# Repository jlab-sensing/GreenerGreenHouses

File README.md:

# JLab - Greener Greenhouses Sensing Project

This repository contains concurrent work for the Greener Greenhouses research project.

## Repository Contents

- **MSP430**
  
    Contains a general library for the [TI MSP430FR5969](https://www.ti.com/tool/MSP-EXP430FR5969?DCMP=mcugen&HQS=ep-mcu-msp-mcugen-mspblog-pf1-en) microcontroller to communicate with the [HDC2021](https://www.ti.com/product/HDC2021?utm_source=google&utm_medium=cpc&utm_campaign=asc-null-null-GPN_EN-cpc-pf-google-wwe&utm_content=HDC2021&ds_k=HDC2021&DCM=yes&gclid=Cj0KCQjwrfymBhCTARIsADXTabmBxpIyiHJQwz-0fqVoGLloWWmzIEXDT699dNn-ivyHtGXB0x-GpR8aAtybEALw_wcB&gclsrc=aw.ds) Temperature and Humidity Sensor.
  
- **PassiveLiFiTag**

    Includes schematic files for a prototype of the Passive LiFi IoT tag using the TI MSP430FR5969 microcontroller

- **RH_T_Replacement_Board**

    Contains .ino test harness and data storage files for HDC2021 sensor testing using Arduino. Also contains Eagle hardware files for the GGH RH/T replacement board
    
- **LoRa_BoosterPack_Registers**

    Contains register names and settings for ETSI CAT1 869MHz. 1.2Kbps, 2-GFSK, 25Khz channel spacing, ETSI EN 300 220 CAT1 setting with the [CC1125 LoRa module Boosterpack](https://www.ti.com/tool/BOOSTXL-CC1125). Register names and values exported from [SmartRFStudio v7.0](https://www.ti.com/tool/SMARTRFTM-STUDIO) for packet Tx/Rx.

- **BeagleBoneBlack**

    Contains source code for Beaglebone Black development, specifically work on SPI to LoRa boosterpack compatability, and ModbusLib test code for server/client side testing.

  ## To Do

  - [x] Create specific README file for each directory
  - [ ] file cleanup - remove defunct or unnecessary files
  - [ ] Update root README when new directories are created
  - [x] Standardize naming conventions for each directory
  - [x] License Project under MIT

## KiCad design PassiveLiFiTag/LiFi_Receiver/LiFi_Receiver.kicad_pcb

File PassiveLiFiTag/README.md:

# PassiveLiFiTag

This directory contains hardware design files for the PassiveLiFiTag. These files are compatible with EAGLE 9.6.2.

## Files
- Library Source\ -- Contains the source files that were used to create the EAGLE library
- PassiveLiFiTag.brd -- PCB layout (not yet added)
- PassiveLiFiTag.lbr -- EAGLE library
- PassiveLiFiTag.sch -- Electrical schematic

## Instructions
**NOTE**: Currently the schematic is not yet finalized. It is populated with major components, but is not connected.

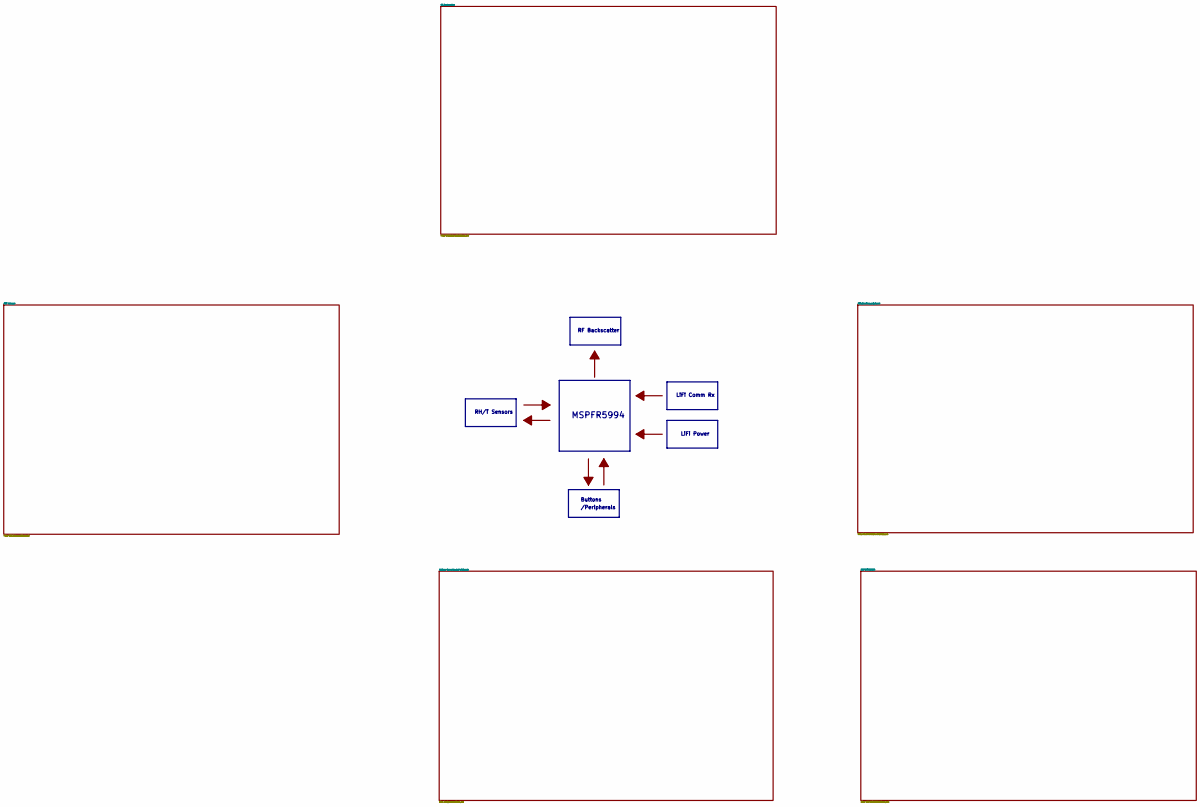
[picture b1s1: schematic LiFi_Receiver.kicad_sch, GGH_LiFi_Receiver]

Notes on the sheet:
RH/T Sensors
/Peripherals
LiFi Comm Rx
MSPFR5994
RF Backscatter
Buttons
LiFi Power

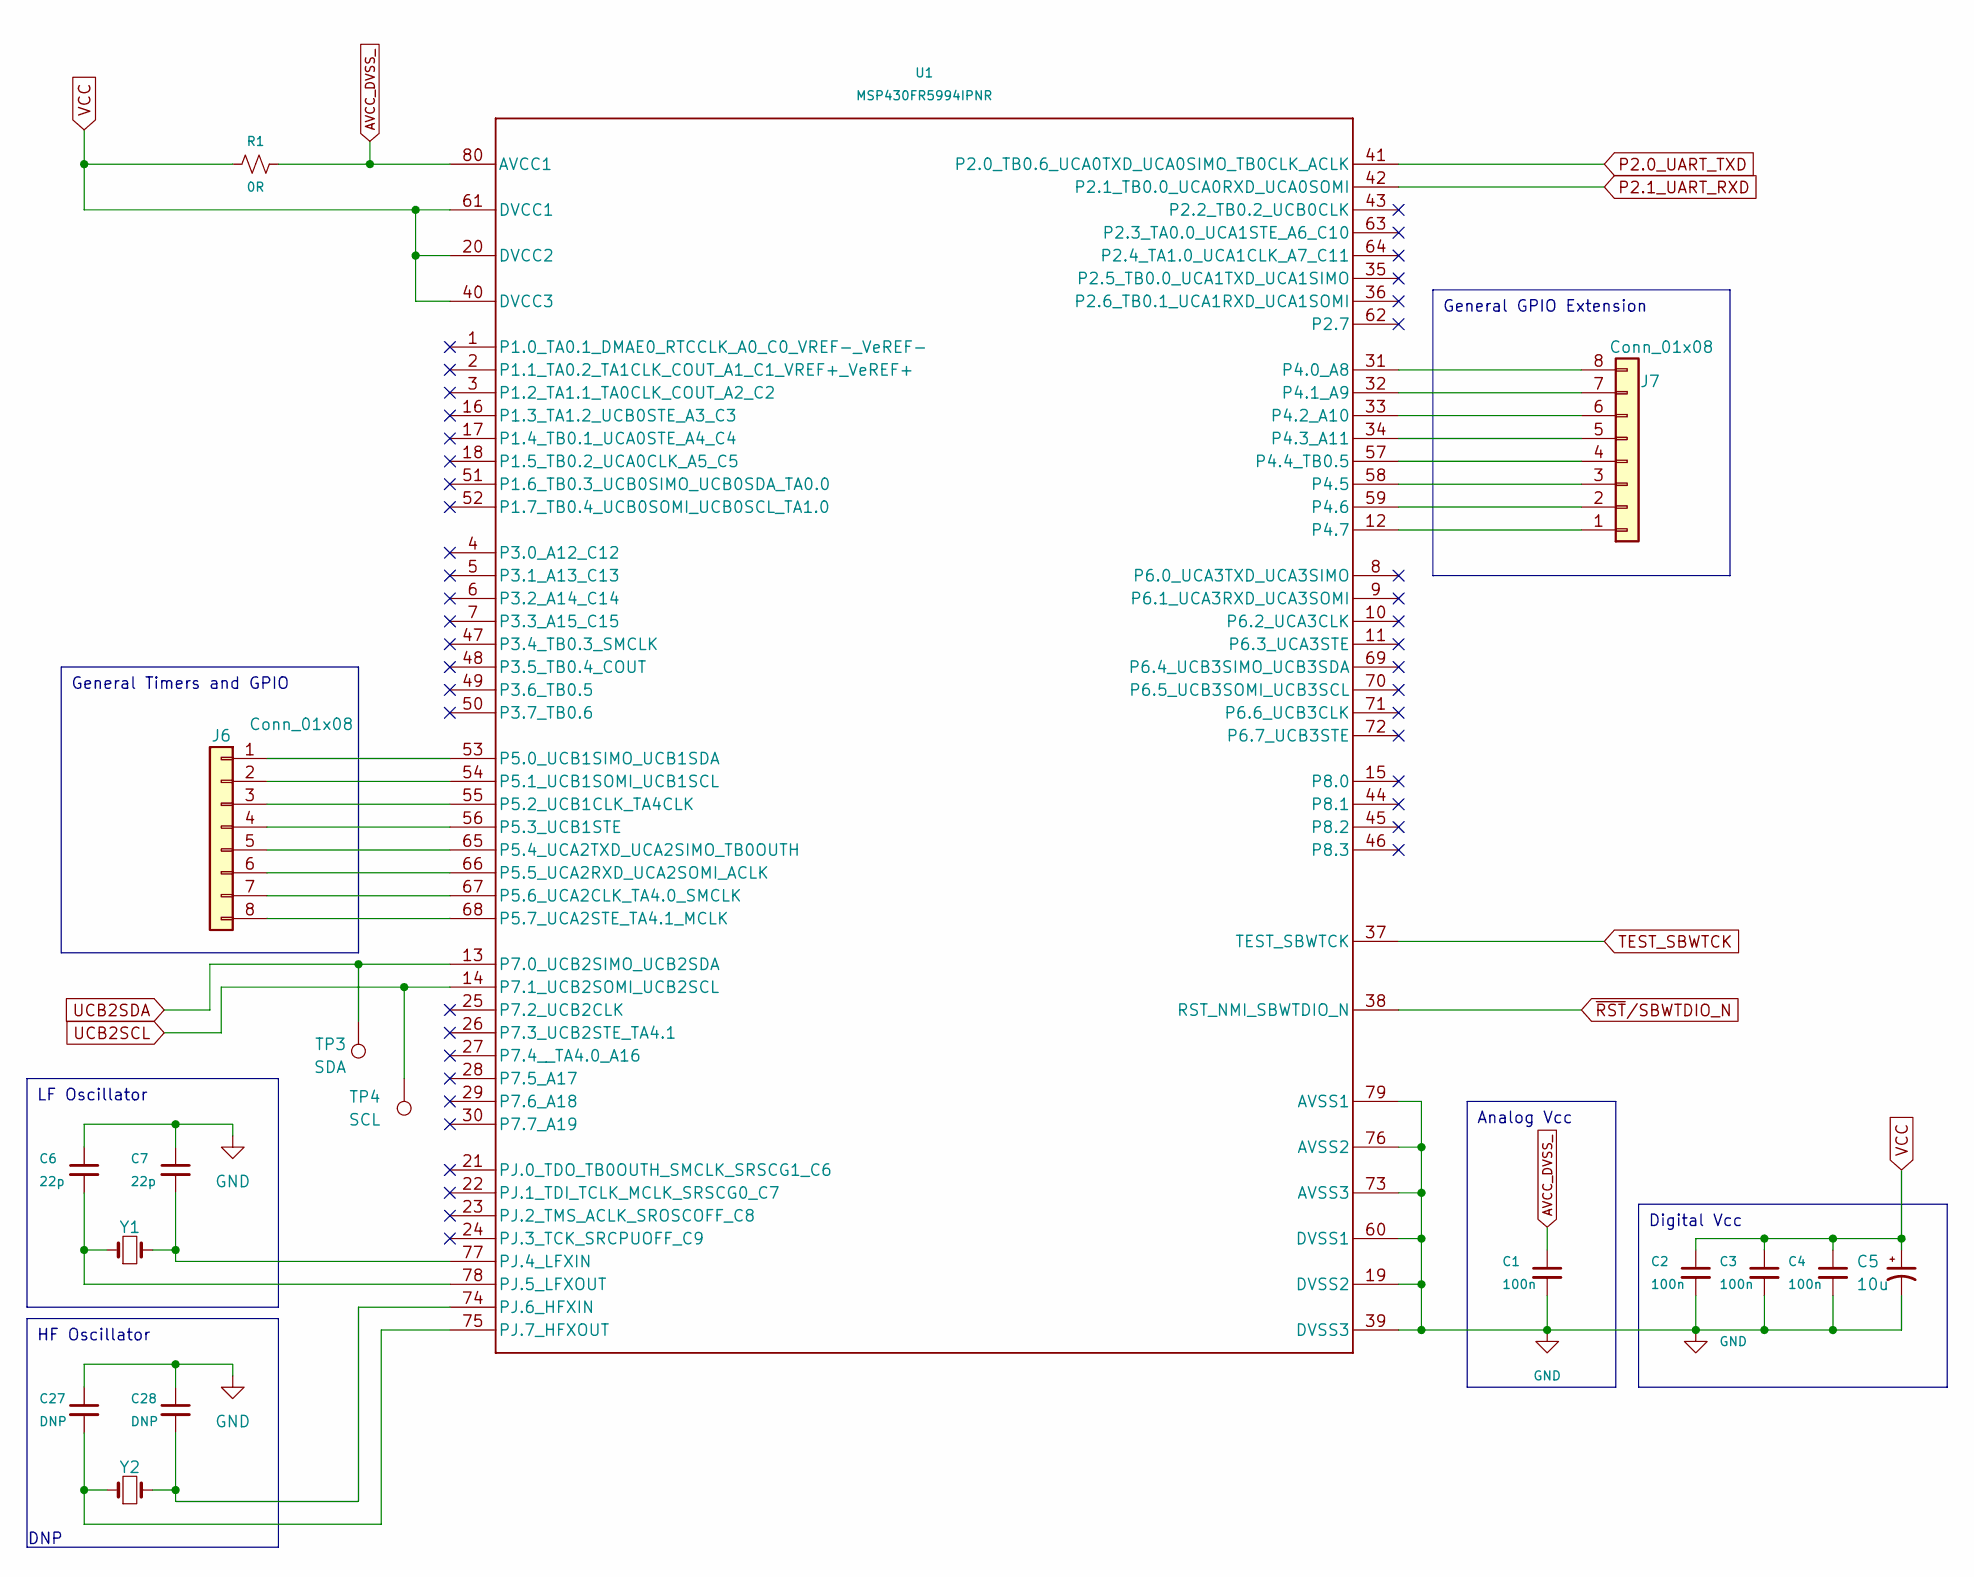
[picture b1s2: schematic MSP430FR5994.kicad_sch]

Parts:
C1, C2, C3, C4: 100n; C_0603_1608Metric
C5: 10u; C_0603_1608Metric
C6, C7: 22p; C_0603_1608Metric
C27, C28: DNP; C_0603_1608Metric
J6, J7: Conn_01x08; PinHeader_2x04_P2.54mm_Vertical
R1: 0R; R_0603_1608Metric
TP3: SDA; TestPoint_Pad_D1.5mm
TP4: SCL; TestPoint_Pad_D1.5mm
U1: MSP430FR5994IPNR; PN0080A_L
Y1, Y2: Crystal_Small; xtal-2

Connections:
AVCC_DVSS_: C1.1, R1.2, U1.80 (AVCC1)
GND: C1.2, C2.2, C3.2, C4.2, C5.2, C6.1, C7.1, C27.1, C28.1, U1.19 (DVSS2), U1.39 (DVSS3), U1.60 (DVSS1), U1.73 (AVSS3), U1.76 (AVSS2), U1.79 (AVSS1); also elsewhere on the board
unnamed: J6.1, U1.53 (P5.0_UCB1SIMO_UCB1SDA)
unnamed: J6.2, U1.54 (P5.1_UCB1SOMI_UCB1SCL)
unnamed: J6.3, U1.55 (P5.2_UCB1CLK_TA4CLK)
unnamed: J6.4, U1.56 (P5.3_UCB1STE)
unnamed: J6.5, U1.65 (P5.4_UCA2TXD_UCA2SIMO_TB0OUTH)
unnamed: J6.6, U1.66 (P5.5_UCA2RXD_UCA2SOMI_ACLK)
unnamed: J6.7, U1.67 (P5.6_UCA2CLK_TA4.0_SMCLK)
unnamed: J6.8, U1.68 (P5.7_UCA2STE_TA4.1_MCLK)
unnamed: J7.1, U1.12 (P4.7)
unnamed: J7.2, U1.59 (P4.6)
unnamed: J7.3, U1.58 (P4.5)
unnamed: J7.4, U1.57 (P4.4_TB0.5)
unnamed: J7.5, U1.34 (P4.3_A11)
unnamed: J7.6, U1.33 (P4.2_A10)
unnamed: J7.7, U1.32 (P4.1_A9)
unnamed: J7.8, U1.31 (P4.0_A8)
unnamed: C7.2, U1.77 (PJ.4_LFXIN), Y1.2
unnamed: C6.2, U1.78 (PJ.5_LFXOUT), Y1.1
unnamed: C28.2, U1.74 (PJ.6_HFXIN), Y2.2
unnamed: C27.2, U1.75 (PJ.7_HFXOUT), Y2.1
P2.0_UART_TXD: U1.41 (P2.0_TB0.6_UCA0TXD_UCA0SIMO_TB0CLK_ACLK); also elsewhere on the board
P2.1_UART_RXD: U1.42 (P2.1_TB0.0_UCA0RXD_UCA0SOMI); also elsewhere on the board
TEST_SBWTCK: U1.37 (TEST_SBWTCK); also elsewhere on the board
UCB2SCL: TP4.1, U1.14 (P7.1_UCB2SOMI_UCB2SCL); also elsewhere on the board
UCB2SDA: TP3.1, U1.13 (P7.0_UCB2SIMO_UCB2SDA); also elsewhere on the board
VCC: C2.1, C3.1, C4.1, C5.1, R1.1, U1.20 (DVCC2), U1.40 (DVCC3), U1.61 (DVCC1); also elsewhere on the board
~RST/SBWTDIO_N: U1.38 (RST_NMI_SBWTDIO_N); also elsewhere on the board

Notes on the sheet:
Analog Vcc
Digital Vcc
General Timers and GPIO
General GPIO Extension
LF Oscillator
HF Oscillator
DNP

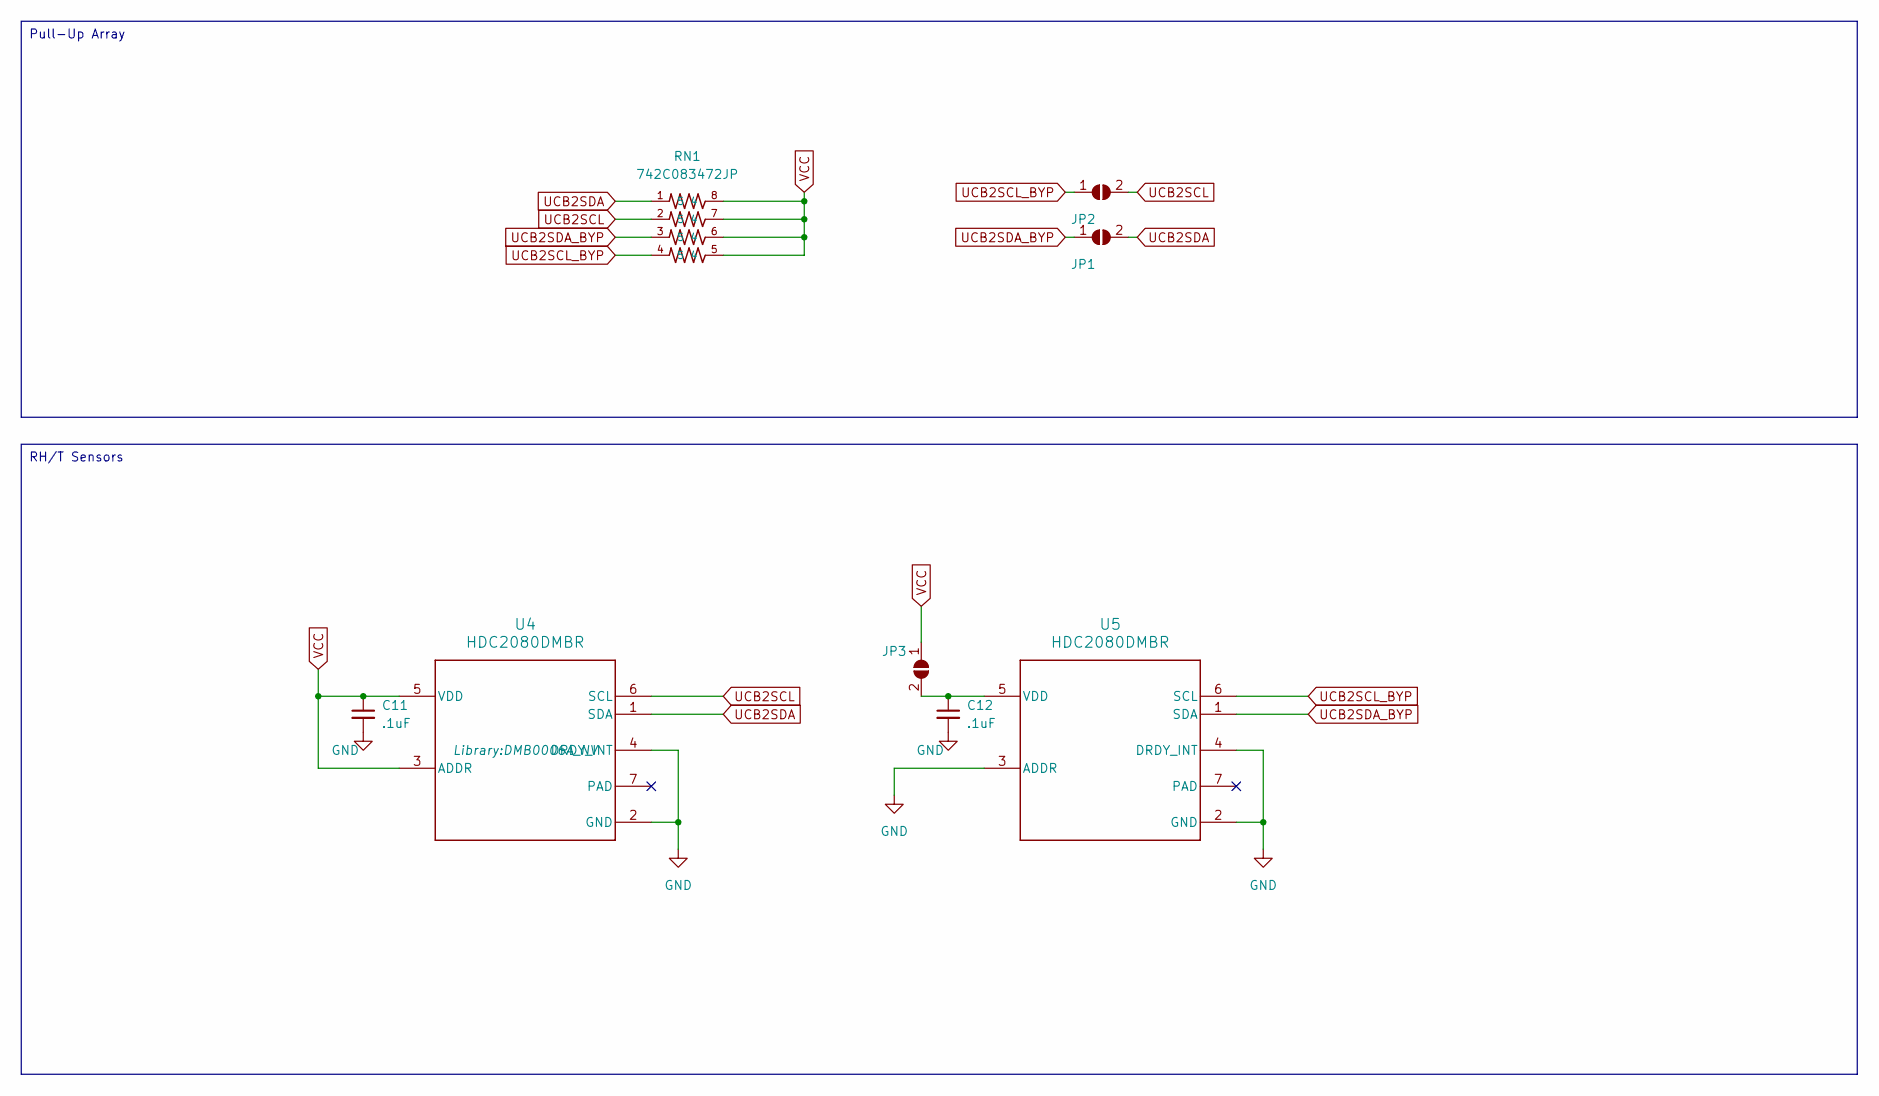
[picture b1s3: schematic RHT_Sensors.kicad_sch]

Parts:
C11, C12: .1uF; C_0603_1608Metric
JP1, JP2, JP3: SolderJumper_2_Open; SolderJumper-2_P1.3mm_Open_TrianglePad1.0x1.5mm
RN1: 742C083472JP; RESCAV80P320X160X70-8N; DigiKey_Part_Number 742C083472JPTR-ND
U4, U5: HDC2080DMBR; DMB0006A_NV

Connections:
GND: C11.2, C12.2, U4.2 (GND), U4.4 (DRDY_INT), U5.2 (GND), U5.3 (ADDR), U5.4 (DRDY_INT); also elsewhere on the board
unnamed: C12.1, JP3.2 (B), U5.5 (VDD)
UCB2SCL: JP2.2 (B), RN1.2 (5), U4.6 (SCL); also elsewhere on the board
UCB2SCL_BYP: JP2.1 (A), RN1.4 (5), U5.6 (SCL)
UCB2SDA: JP1.2 (B), RN1.1 (5), U4.1 (SDA); also elsewhere on the board
UCB2SDA_BYP: JP1.1 (A), RN1.3 (5), U5.1 (SDA)
VCC: C11.1, JP3.1 (A), RN1.5 (4), RN1.6 (4), RN1.7 (4), RN1.8 (4), U4.3 (ADDR), U4.5 (VDD); also elsewhere on the board

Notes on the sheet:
RH/T Sensors
Pull-Up Array

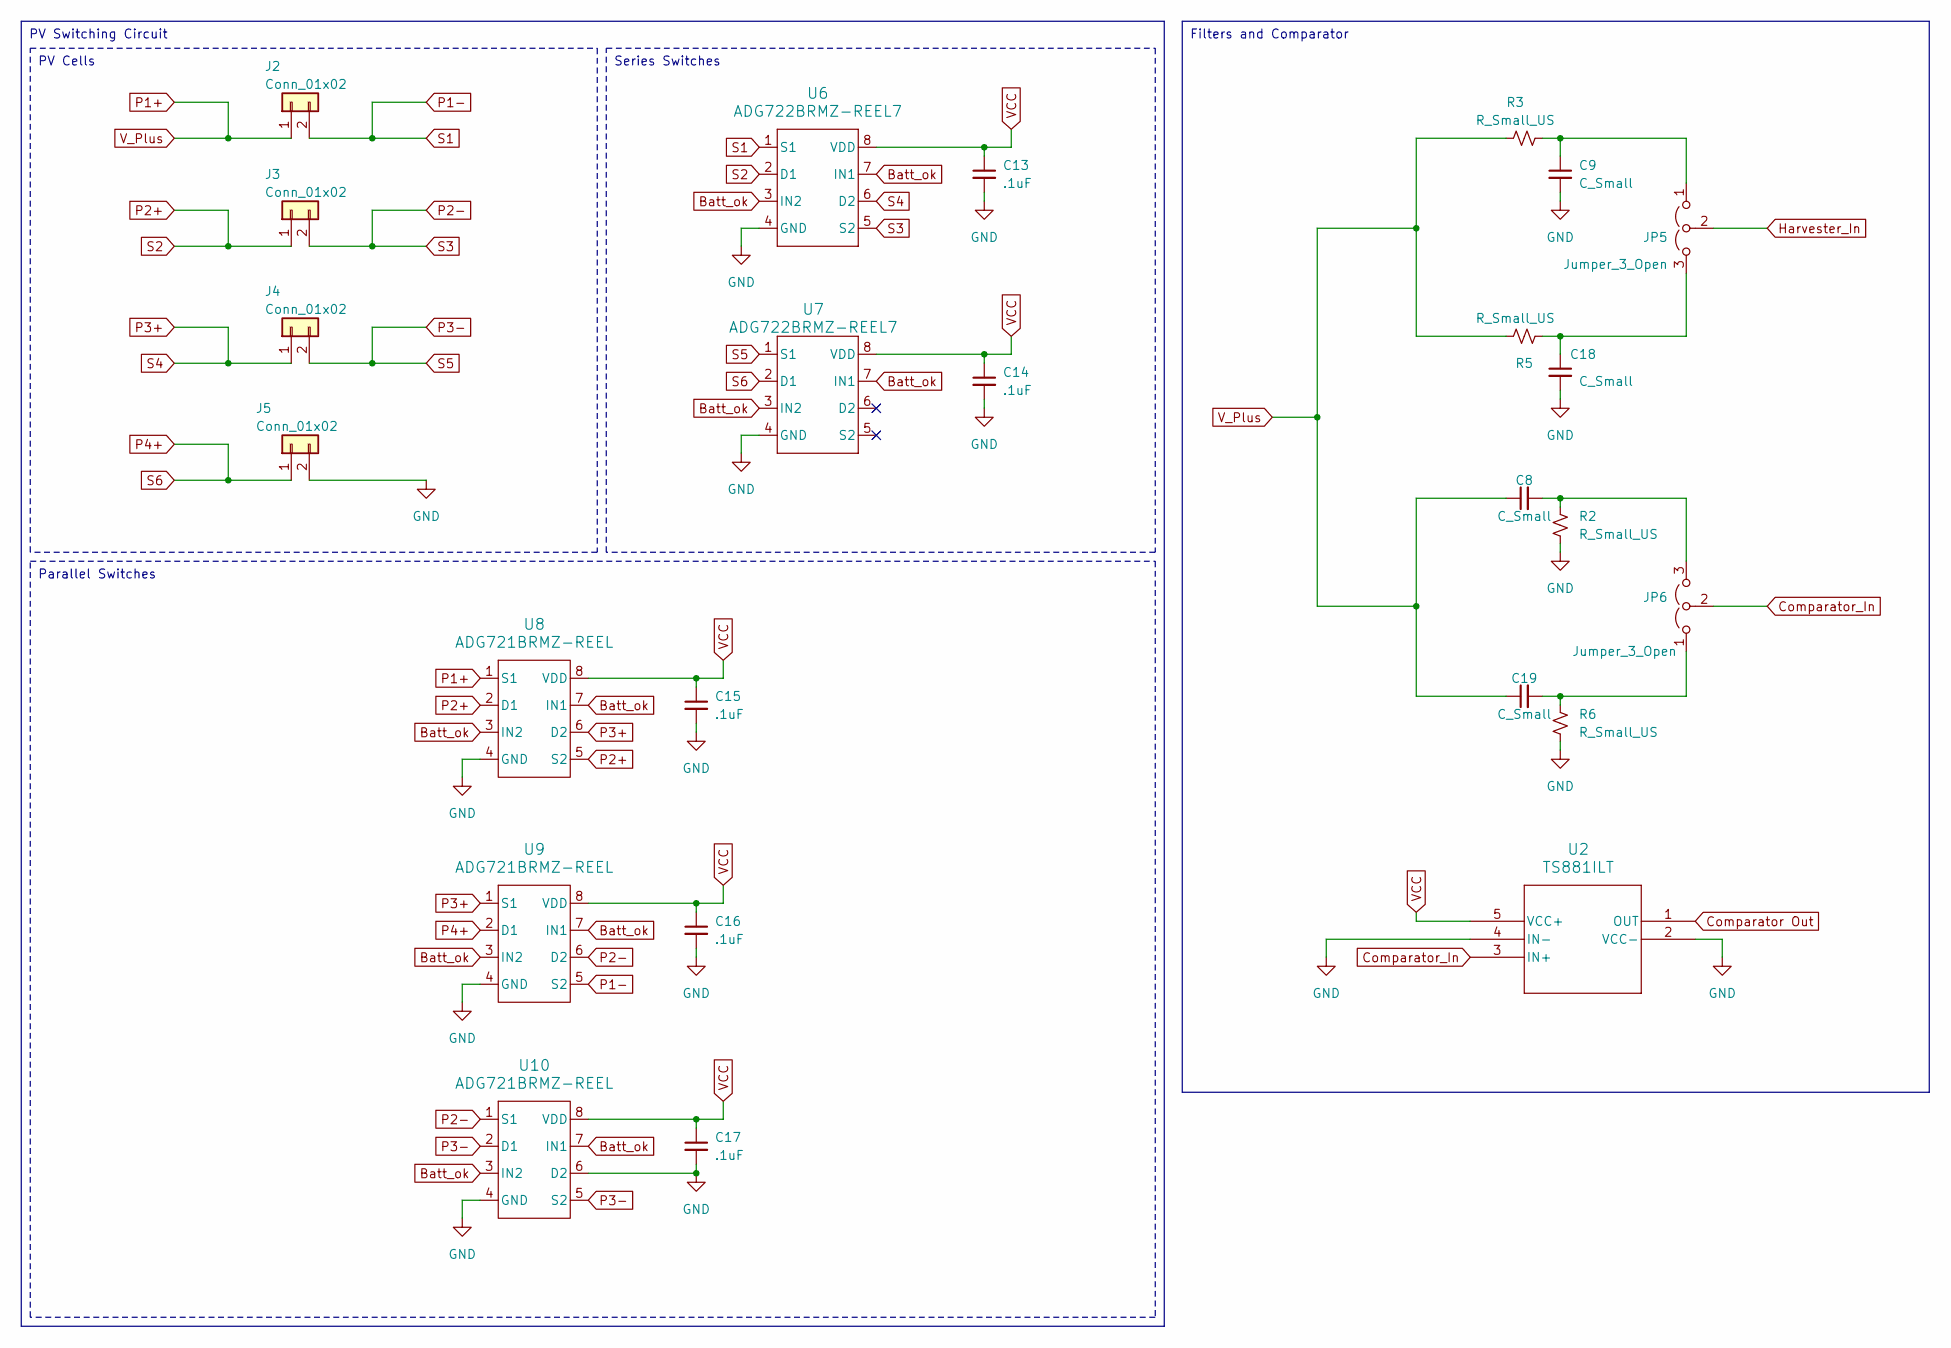
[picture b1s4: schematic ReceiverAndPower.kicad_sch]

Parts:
C8, C9: C_Small; C_0603_1608Metric
C13, C14, C15, C16, C17: .1uF; C_0603_1608Metric
C18, C19: C_Small; PinSocket_1x02_P2.54mm_Vertical
J2, J3, J4, J5: Conn_01x02; PinSocket_1x02_P2.54mm_Vertical
JP5, JP6: Jumper_3_Open; PinHeader_1x03_P2.54mm_Vertical
R2, R3: R_Small_US; R_0603_1608Metric
R5, R6: R_Small_US; PinSocket_1x02_P2.54mm_Vertical
U2: TS881ILT; SOT23-5_TS881_TEX
U6, U7: ADG722BRMZ-REEL7; RM_8_ADI-M
U8, U9, U10: ADG721BRMZ-REEL; RM_8_ADI

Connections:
Batt_ok: U6.3 (IN2), U6.7 (IN1), U7.3 (IN2), U7.7 (IN1), U8.3 (IN2), U8.7 (IN1), U9.3 (IN2), U9.7 (IN1), U10.3 (IN2), U10.7 (IN1); also elsewhere on the board
Comparator Out: U2.1 (OUT)
Comparator_In: JP6.2 (C), U2.3 (IN+)
GND: C9.2, C13.2, C14.2, C15.2, C16.2, C17.2, C18.2, J5.2, R2.2, R6.2, U2.2 (VCC-), U2.4 (IN-), U6.4 (GND), U7.4 (GND), U8.4 (GND), U9.4 (GND), U10.4 (GND), U10.6 (D2); also elsewhere on the board
Harvester_In: JP5.2 (C); also elsewhere on the board
unnamed: C9.1, JP5.1 (A), R3.2
unnamed: C18.1, JP5.3 (B), R5.2
unnamed: C19.2, JP6.1 (A), R6.1
unnamed: C8.2, JP6.3 (B), R2.1
P1+: C8.1, C19.1, J2.1, R3.1, R5.1, U8.1 (S1)
P1-: J2.2, U6.1 (S1), U9.5 (S2)
P2+: J3.1, U6.2 (D1), U8.2 (D1), U8.5 (S2)
P2-: J3.2, U6.5 (S2), U9.6 (D2), U10.1 (S1)
P3+: J4.1, U6.6 (D2), U8.6 (D2), U9.1 (S1)
P3-: J4.2, U7.1 (S1), U10.2 (D1), U10.5 (S2)
P4+: J5.1, U7.2 (D1), U9.2 (D1)
VCC: C13.1, C14.1, C15.1, C16.1, C17.1, U2.5 (VCC+), U6.8 (VDD), U7.8 (VDD), U8.8 (VDD), U9.8 (VDD), U10.8 (VDD); also elsewhere on the board

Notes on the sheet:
Filters and Comparator
PV Switching Circuit
Parallel Switches
PV Cells
Series Switches

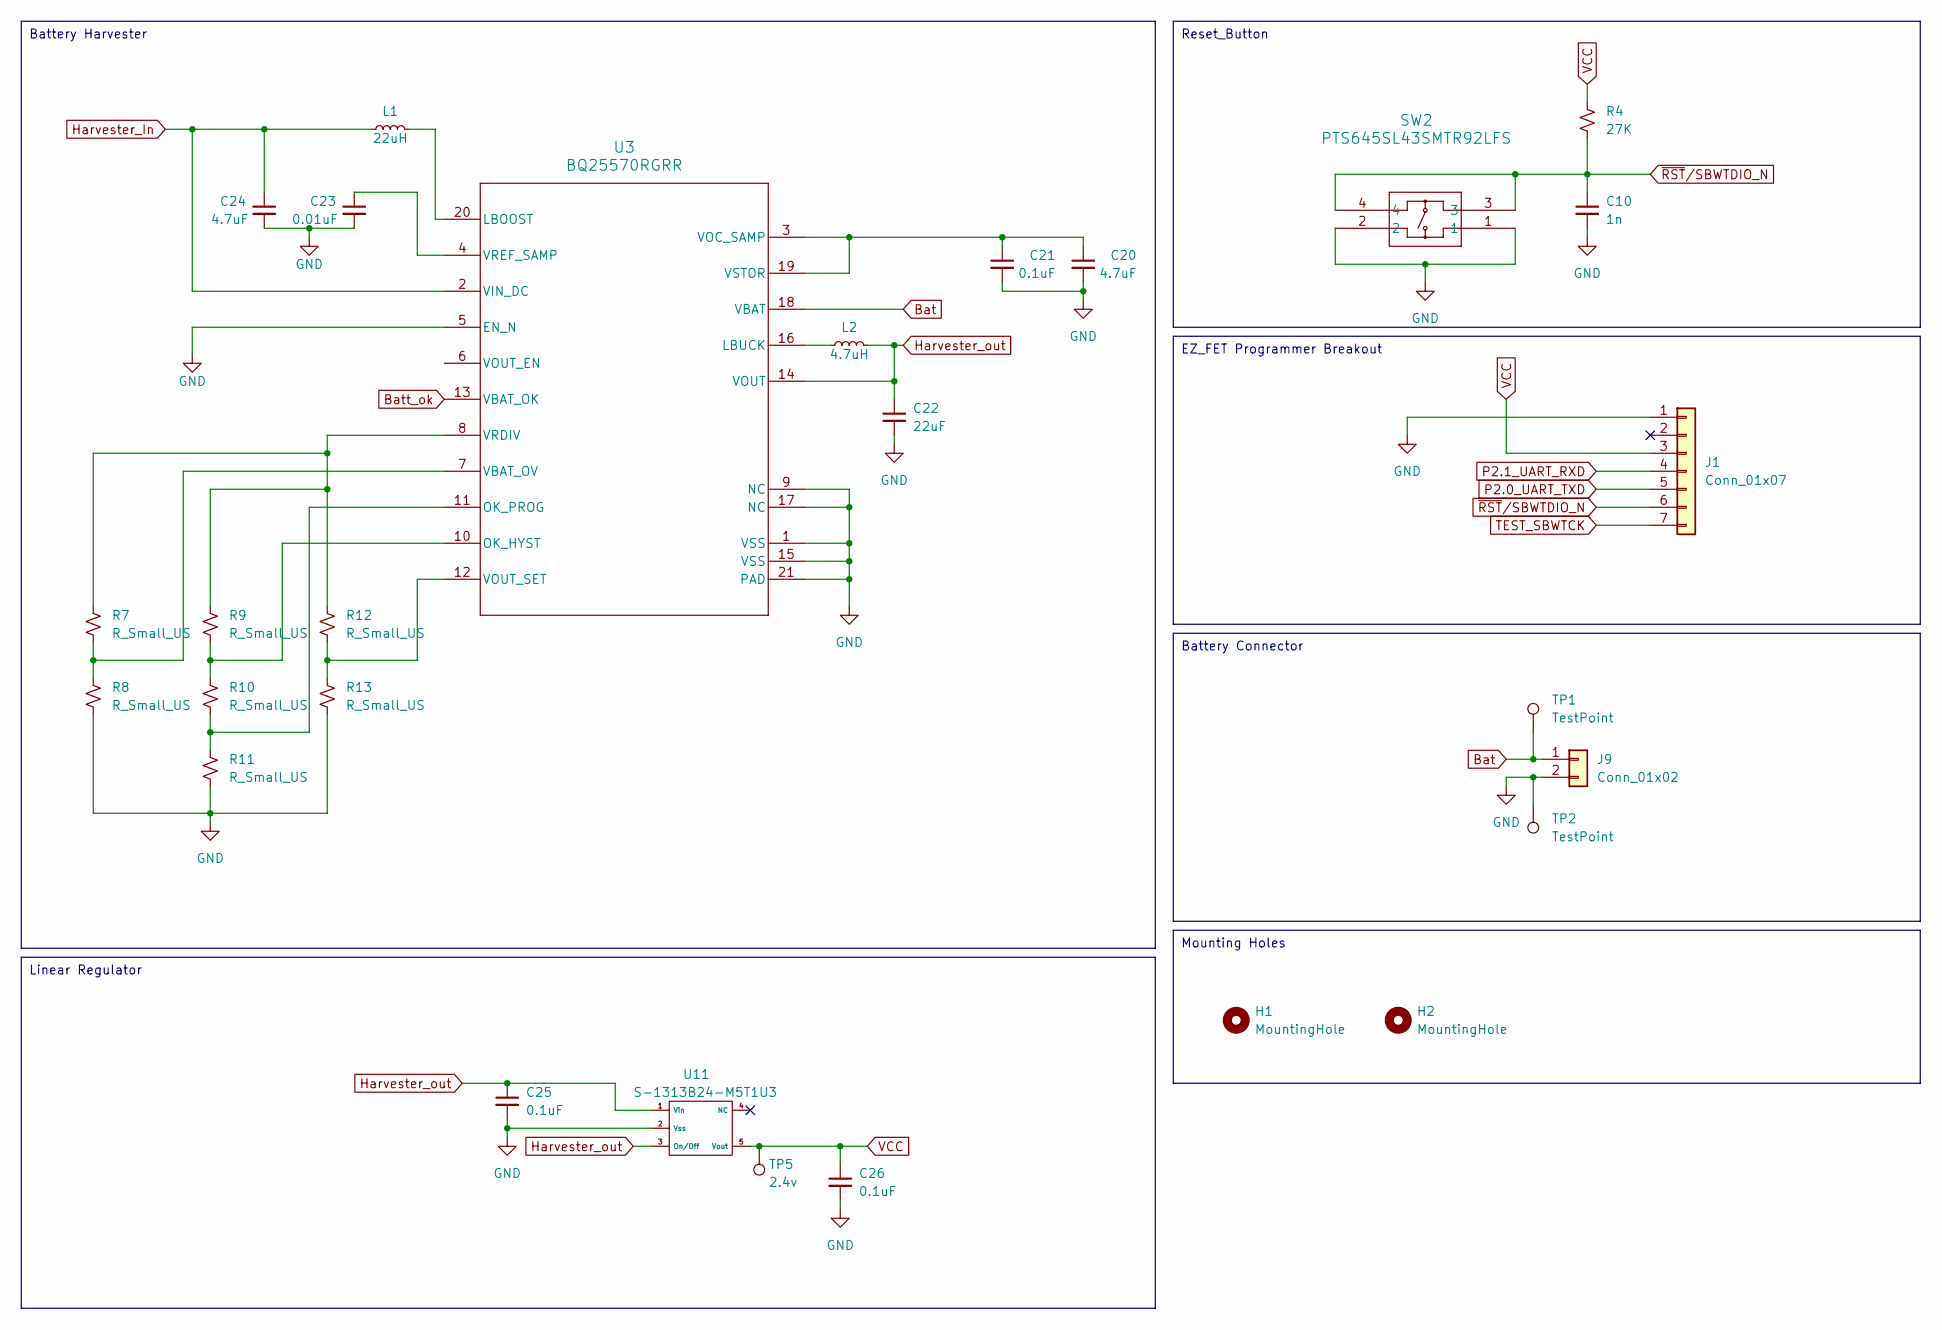
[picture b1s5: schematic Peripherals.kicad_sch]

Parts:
C10: 1n; C_0603_1608Metric
C20, C24: 4.7uF; C_0603_1608Metric
C21, C25, C26: 0.1uF; C_0603_1608Metric
C22: 22uF; C_0603_1608Metric
C23: 0.01uF; C_0603_1608Metric
H1, H2: MountingHole; MountingHole_2.2mm_M2
J1: Conn_01x07; PinSocket_1x07_P2.54mm_Vertical
J9: Conn_01x02; PinSocket_1x02_P2.54mm_Vertical
L1: 22uH; L_0603_1608Metric
L2: 4.7uH; L_0603_1608Metric
R4: 27K; R_0603_1608Metric
R7, R8, R9, R10, R11, R12, R13: R_Small_US; R_0603_1608Metric
SW2: PTS645SL43SMTR92LFS; PTS645SL43SMTR92LFS_CNK-M
TP1, TP2: TestPoint; TestPoint_Pad_D1.5mm
TP5: 2.4v; TestPoint_Pad_D1.5mm
U3: BQ25570RGRR; Bat_Harv1
U11: S-1313B24-M5T1U3; SOT-23-5

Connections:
Bat: J9.1, TP1.1, U3.18 (VBAT)
Batt_ok: U3.13 (VBAT_OK); also elsewhere on the board
GND: C10.2, C20.2, C21.2, C22.2, C23.2, C24.2, C25.2, C26.2, J1.1, J9.2, R8.2, R11.2, R13.2, SW2.1, SW2.2, TP2.1, U3.1 (VSS), U3.5 (EN_N), U3.9 (NC), U3.15 (VSS), U3.17 (NC), U3.21 (PAD), U11.2 (Vss); also elsewhere on the board
Harvester_In: C24.1, L1.2, U3.2 (VIN_DC); also elsewhere on the board
Harvester_out: C22.1, C25.1, L2.1, U3.14 (VOUT), U11.1 (Vin), U11.3 (On/Off)
unnamed: L1.1, U3.20 (LBOOST)
unnamed: L2.2, U3.16 (LBUCK)
unnamed: R9.2, R10.1, U3.10 (OK_HYST)
unnamed: R10.2, R11.1, U3.11 (OK_PROG)
unnamed: R7.2, R8.1, U3.7 (VBAT_OV)
unnamed: C20.1, C21.1, U3.3 (VOC_SAMP), U3.19 (VSTOR)
unnamed: R12.2, R13.1, U3.12 (VOUT_SET)
unnamed: R7.1, R9.1, R12.1, U3.8 (VRDIV)
unnamed: C23.1, U3.4 (VREF_SAMP)
P2.0_UART_TXD: J1.5; also elsewhere on the board
P2.1_UART_RXD: J1.4; also elsewhere on the board
TEST_SBWTCK: J1.7; also elsewhere on the board
VCC: C26.1, J1.3, R4.1, TP5.1, U11.5 (Vout); also elsewhere on the board
~RST/SBWTDIO_N: C10.1, J1.6, R4.2, SW2.3, SW2.4; also elsewhere on the board

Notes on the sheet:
Battery Harvester
Mounting Holes
Reset_Button
Linear Regulator
Battery Connector
EZ_FET Programmer Breakout

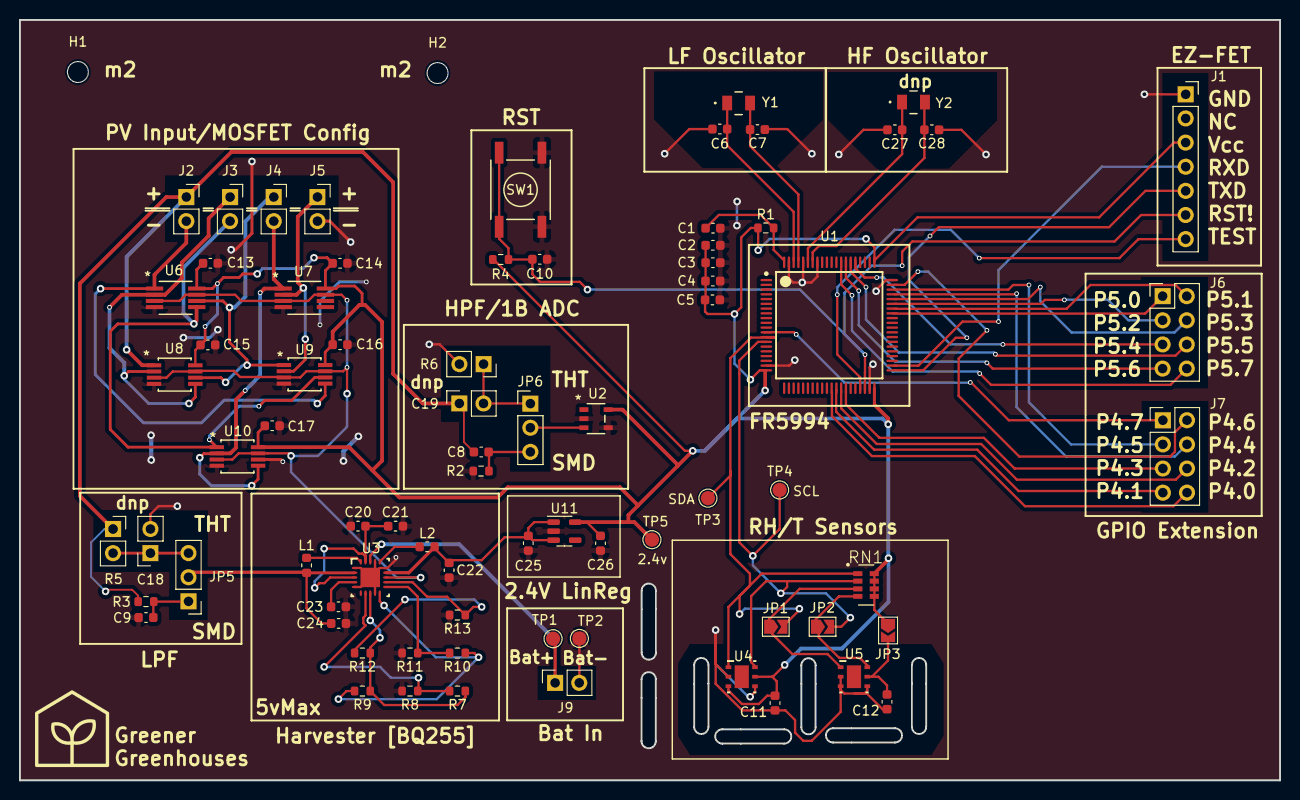
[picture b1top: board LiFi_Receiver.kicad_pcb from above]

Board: 2 copper layers, 132.6 x 80.0 mm, 78 parts (0 on the bottom side), 57 nets.

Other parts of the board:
SW1: PTS645SL43SMTR92LFS; PTS645SL43SMTR92LFS_CNK-M

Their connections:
GND: SW1.1, SW1.2; also elsewhere on the board
~RST/SBWTDIO_N: SW1.3, SW1.4; also elsewhere on the board

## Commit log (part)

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2023-07-12 gitignore backups"
2023-07-12 PassiveLiFiTag empty schematic
2023-07-13 PassiveLiFi parts placed and library
2023-07-17 created replacement board folder for replacement board files
2023-07-17 added RH_T Test harness
2023-07-18 Added Matlab code for temp/humidity profile graph
2023-07-18 added RH/T arduino I2C Library
2023-07-18 started writing code for test harness, need to add sd card data reading portion
2023-07-18 Added text files for HVT data
2023-07-18 Created folder for HVT data files
2023-07-18 added text files for sd card to read/write to and SPI lib for communication
2023-07-19 HVT code ~should~ be done and ready to run
2023-07-24 added matlab code that compares power consumption of 3 sensors
2023-07-25 edit to supply current to one of the sensors
2023-07-25 edits to voltages
2023-07-27 initial test code complete. need to add softwire functionality to poll both I2C sensors
2023-07-27 Initial (backyard) RH/T test raw data added
2023-07-28 added sketch of digital I2C attempt
2023-08-14 adding MSP430 sensor sketch, Matt's github does not work
2023-08-16 Working Temperature polling code for MSP430 with CCS
2023-08-16 whole i2c project
2023-08-16 Created project with headers for i2c and hdc2021
2023-08-17 Created CCS project for communication between MSP430FR5969 and HDC2021 RH/T Sensor
2023-08-17 removed redundant and unecessary ccs project directories
2023-08-17 removed unneccesary read/write commands as they will be abstracted through functions utilizing MSP430_I2C
2023-08-17 Removed unnnecessary #defines and added function descriptions
2023-08-17 Added i2c header and beginning i2c.c file, removed master/slave terminology
2023-08-17 Configuration functions for HDC2080 done
2023-08-17 Rough draft of I2C ready to integrate and test
2023-08-17 main.c will poll for sensors device id and manufacturer id and store in memory
2023-08-17 Added extern variables to main for proper Tx and Rx behavior
2023-08-17 Matt check ReceiveBuffer
2023-08-17 small I2C lib adjustment
2023-08-17 update on buffers
2023-08-17 register transceiving is done in sensor library
2023-08-17 sensor reset written
2023-08-17 Created README skeleton and cleaned up functions
2023-08-17 removed .txt readme to replace with a .md
2023-08-18 added comments to .c library file
2023-08-18 reverting arduino test harness back to original code after accidental delete
2023-08-18 created README for root directory
2023-08-18 Create README.md for PassiveLiFiTag
2023-08-18 Updated root README.md
2023-08-18 Removed old dummy data directory
2023-08-18 Create LICENSE for the repository
2023-08-21 Removed extern variable from HDC2021 library and main.c
2023-08-21 UART example added to repo
2023-08-21 Added UART lib skeleton and uart example to correct folder
2023-08-21 crude rendition of UART library finished, still have to use different clock and test
2023-08-21 added UART libraries to new project
2023-08-21 most recent work
2023-08-21 moved UART library back to I2c project, deleted UART project
2023-08-21 remove uart main
2023-08-22 more work debugging, havent gotten it to work yet
2023-08-22 added TI MSP430 Driver Library
2023-08-22 add TI proprietary UART driver attempt (DOES NOT WORK EITHER)
2023-08-23 added headers for raw sensor readings, will be used to send over LoRa and avoid FP operations on MSP
2023-08-23 removed UART library files because they are in other CCS project
2023-08-23 added offset adjust functions for temp and humidity as well as functions that return raw sensor reading in uint8_t format
2023-08-23 BBB test files
2023-08-23 UART lib finally works, issue was misplaced or-assign symbol
2023-08-23 Changed I2C clock operation from 16MHz -> 8MHz
2023-08-23 added more test files from the successful SPI BME280 device ID read test
2023-08-23 reorganized
2023-08-23 lora registers from smartrf studio 7
2023-08-23 LoRa test read/write and burst defines
2023-08-24 attempted to interconnect UART with hdc2021 for data printing
2023-08-24 expanded sensor functions by adding 2 functions that enable and disable the sensor heating element
2023-08-24 need to fix timer declarations
2023-08-24 UART comms with sensor now work
2023-08-24 added humidity measurements as well
2023-08-24 added code comments, slight issue with sensor? temp and humidity dont change when continuously polling, but when resetting value changes first measurement and then doesnt change anymore after continu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
2023-08-24 Update root README
2023-08-25 reorganized and added config-pin scripts
2023-08-25 Added readme
2023-08-25 updated readme with attribution
2023-08-28 work on UART, attempting to implement circular buffer as a more efficient method of parsing buffers for transmission
2023-08-28 UART driver now works with circular buffer (with small delay between char transmissions)
2023-08-28 added comments
2023-08-28 CC1125 demo not building for BBB
2023-08-28 Modification based on SWRC253E for CC1125, compiles for BBB
2023-08-28 comments and TX buffer interrupt addition
2023-08-28 changes in main example
2023-08-28 smartrf studio 7 register values for the boosterpack, and LoRa boosterpack SPI test (register read/write/read) for BBB
2023-08-29 blank readme and reorganized config-pin scripts
2023-08-29 readme for BBB LoRa boosterpack folder
2023-08-29 wiring diagram
2023-08-29 readme updated to reflect config-pin reorganization
2023-08-29 libmodbus test files
2023-08-30 UART putc()/puts() working for terminal output (9600, 8-N-1)
2023-08-30 master and slave test libmodbus
2023-08-30 BBB modbus slave incorrect reply or malformed output
2023-08-30 updates to readme in this directory for higher accuracy on contents
2023-08-30 added fun message
2023-08-31 Not completely working yet
2023-09-01 device number function
2023-09-01 edits, doesnt work
2023-09-01 SPI working on MSP430 to communicate with LoRa boosterpack
2023-09-01 Uart working in conjunction with LoRa SPI
2023-09-01 SPI UART test formatting and code comments, removed UART_example and LaunchPad_trx_demo directories due to old, outdated, and non functioning code
2023-09-01 renamed spi uart directory
2023-09-01 BBB libmodbus master command and slave reply ok
2023-09-01 reorganized libmodbus old test files and added readme (no image)
2023-09-01 LoRa Module Communication almost complete, register initializations tested
2023-09-05 Added uart lib for easier client use, only has putc() and puts()
2023-09-05 created initSpi() in main.c so main function is cleaner
2023-09-05 Created better looking/clearer terminal test harness
2023-09-05 added basic Rx test, will be tested later today
2023-09-05 LoRa boosterpack registers are the same for packet txrx
2023-09-05 fixed register name to 112X
2023-09-05 Communication between LoRa modules established
2023-09-05 added allSettings (don't access .data), modified main (untested) for RX
2023-09-06 comments and code formatting
2023-09-06 removed copy of cc1125 directory and added readme to final SPI attempt
2023-09-06 adding Tx code
2023-09-06 moved InitUart to uart library instead of temp main
2023-09-06 fixed naming convention
2023-09-06 actually fixed issue
2023-09-06 Tim taking over Tx
2023-09-06 added new directory for board files
2023-09-06 cleaning up files for board data/sch
2023-09-06 removed empty/unneccessary directory
2023-09-06 bbb rx, only 1 byte rx?
2023-09-07 got RF transmission to work, no CRC error anymore by setting fixed message length in RF register configurations
2023-09-07 fixed last commit to have no errors/warnings
2023-09-07 MSP430 Tx working 100%
2023-09-07 attempting to integrate RH/T
2023-09-07 added switch statemnet for easier switching between TX and RX testing mode
2023-09-07 HDC2080 working with uart printing, need to move to LoRa
2023-09-07 removed unecessary comments, and added test case selector
2023-09-08 Moved SPI to EUSCIA1 from EUSCIB0
2023-09-08 ready for packet creation function
2023-09-08 added packet creator function in cc112x_spi library
2023-09-09 BBB tx 'test' (fixed 4 byte) to smartrf OK, still rx fifo error on BBB
2023-09-11 BBB test code for monitoring MARCSTATE register correctly increments RX FIFO length
2023-09-11 Finished packet creation and MSP->BBB comms, need to clean up code
2023-09-11 rxlogger for BBB to write temp/humidity data from MSP430 to file
2023-09-11 put all packet creation lines into unified function
2023-09-11 cleaning up main.c and implementing power saving changes
2023-09-11 finished cleaning up/commenting main_tester.c, need to add LPM in intterupt and while loop
2023-09-11 rxlogger with lora, logging, and modbus reply (modbus untested). may segfault if MAP_SIZE_xxxx are set too low
2023-09-12 implemented LowPowerMode3. Now wakes up to take measurement and goes back to sleep
2023-09-12 formatting and function comments, added packet unpacker function if necessary to unpack packets
2023-09-12 added bit masking to constructor, timers ARE MESSED UP
2023-09-12 Updated packet parser to calculate temperature and humidity based on the upper 14 bits
2023-09-12 added csv logging based on unix time
2023-09-13 removed destroy packet, not necessary :(
2023-09-13 changed bit shift in packetCreate to discord last 2 bits and include first 2 bits instead
2023-09-13 nonblocking modbus receive (build libmodbus from source and adjust indication timeout), basic modbus map modification
2023-09-13 added define to change packet length easily
2023-09-13 equalizing local and remote README version
2023-09-13 LPM3 working with sensor Tx
2023-09-14 Created github onboarding
2023-09-14 renamed LoRa test harness file
2023-09-14 removed defunct Booster_Pack_LoRa_SPI, to remove confusion and is unecessary
2023-09-14 added folder for images and assets
2023-09-14 change to readme :
2023-09-14 Update README.md, from different computer
2023-09-15 fixed parameter order for modbus_init to match parameter order of modbus_mapping_new
2023-09-15 rxlogger fixed modbus_mapping_new and modbus_init parameter order
2023-09-15 removed hal_defs and hal_types with stdint
2023-09-15 rxlogger readme
2023-09-17 added wiring image to github to display in readme
2023-09-18 readmes for BBB
2023-09-18 minor readme changes, added comments to some parts of the code, and return values for init functions
2023-09-18 renamed executable to rxlogger
2023-09-18 readme clarifications on debian libmodbus prebuilt incompatibility
2023-09-19 BBB setup readme, and rxlogger readme update
2023-09-21 readme LiFi control
2023-09-21 readme formatting fixes
2023-09-21 readme libmodbus
2023-09-25 mac USB fix
2023-10-02 added eth0 alias fix instructions to prevent wlan0 default route clobbering
2023-10-02 fixed links, recommend eth0 alias method
2023-10-11 gpio testing for maximizing frequency on the main processor
2023-10-12 direct memory map access to gpio registers results in 360 ns period. faster speeds must be done on PRU
2023-10-12 extended led direct memory map method to do two pins (same chip) alternating
2023-10-13 readme note on disabling strict host key checking
2023-10-13 moved GPIO_test to BBB, updated rxlogger wiring for SYS_5V, cleaned up rxlogger main globals inits prints
2023-10-14 added expected routing table to readme
2023-10-14 GPIO_test brief
2023-10-16 moved modbus map printing to only trigger if a packet was received, also added some sample data received from the MSP
2023-10-19 pru example with 5ns pin access time
2023-10-24 upchirp example
2023-10-25 upchirp with log(?) shifting exhibits significant ringing
2023-10-31 ecr! 1 command to re-enable DC11 response
2023-11-01 added crontab instructions for automation
2023-11-02 manual bootup sequence, which does not solve the calibration issue
2023-11-07 c89 --> c99, 6 byte packet format, disabled debug print messages in main loop
2023-11-07 updated to 6 byte packet format
2024-01-12 Added (incredibly) simple code for linear chirps on EttusN200 USRP
2024-01-17 re-added uart files, idk why they were removed
2024-01-18 Ported relevent FR5969 code to FR994
2024-01-25 Started Hardware design for LiFi Receiver
2024-01-29 Added some small peripherals and voltage supplies/decoupling caps
2024-01-29 Continuing to update Hardware Design
2024-01-30 hopefully fixed git errors
2024-02-07 updating changes
2024-02-07 added Updates
